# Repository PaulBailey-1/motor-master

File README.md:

# MotorMaster
This is a board designed to easily command FRC motors for testing or prototyping. It currently supports motors with the Talon FX motor controller. This repo contains the board schematics, PCB layout, and firmware for the board. 

## Features
It features 2 PWM channels that can be connected directly to the CAN connectors of the motor to command a duty cycle. Pressing the test button will output a 50% duty cycle on both PWM channels.  

The board can also be connected to motors through the CAN bus. Connect one end of the CAN chain to the CAN connector on the board and the other end to the TERM connector, or use another termination resistor. 
NOTE: CAN functionality is still experimental and may not work, feel free to work on it.

The e-stop button will prevent the board from outputting any commands until the MCU is reset with the reset button. 

The EXT pins can be used to connect an external input, like a switch or button, to provide additional control such as driving a motor or as an e-stop. The functionality must be added to the code, by default it does nothing.

The board can be powered through the USB C port, or from the power terminal off of a 12V battery. The board does not supply the motor with power, but it is important that it shares ground with the motor. 

The board is designed to be used over Bluetooth with its accompanying app, the source of which is here: https://github.com/PaulBailey-1/motor-master-app  
It is a cross-platform app and so should be able to be compiled for Android and iOS, but it has only been tested for Android. 

## Manufacturing
Board gerbers exported for manufacture by OSHPark are included in the repo, otherwise, the board can be opened in KiCad to export for manufacture. The BOM can be ordered from either Mouser or DigiKey.  

The FTDI header (J5) and the EXT header (J6) are optional. The USBC TVS diode (D2) may also be omitted since it is hard to solder without bridges, although it does make the USB lines vulnerable to damage from ESD. The USB C may also be omitted entirely (J1 & D2), and the board can be programmed through the FTDI header. 

To assemble the board, a stencil can be ordered and used to apply solder paste to the pads. The solder then may be reflowed in an oven or with hot air. It may also be possible to have it assembled by the PCB fab house.

## Programming
Dependencies:
* CAN by Sandeep Mistry v0.3.1
* ESP32Servo by Kevin Harrington & John K. Bennett v3.0.5

To program the board, connect to it with USB C or with an FTID adapter and program it with the Arduino IDE. Install the ESP32 boards and the required libraries, select 'ESP32S3 Dev Module' as the board, and upload.  

The name of the board over Bluetooth can have a postfix added to it in the code to help distinguish it.
The first time the board is programmed after being assembled, the Boot button must be held from when it is plugged until it has been flashed.
For debugging over USB C make sure the 'USB CDC On Boot' option is enabled so that you can get logging over the serial port.

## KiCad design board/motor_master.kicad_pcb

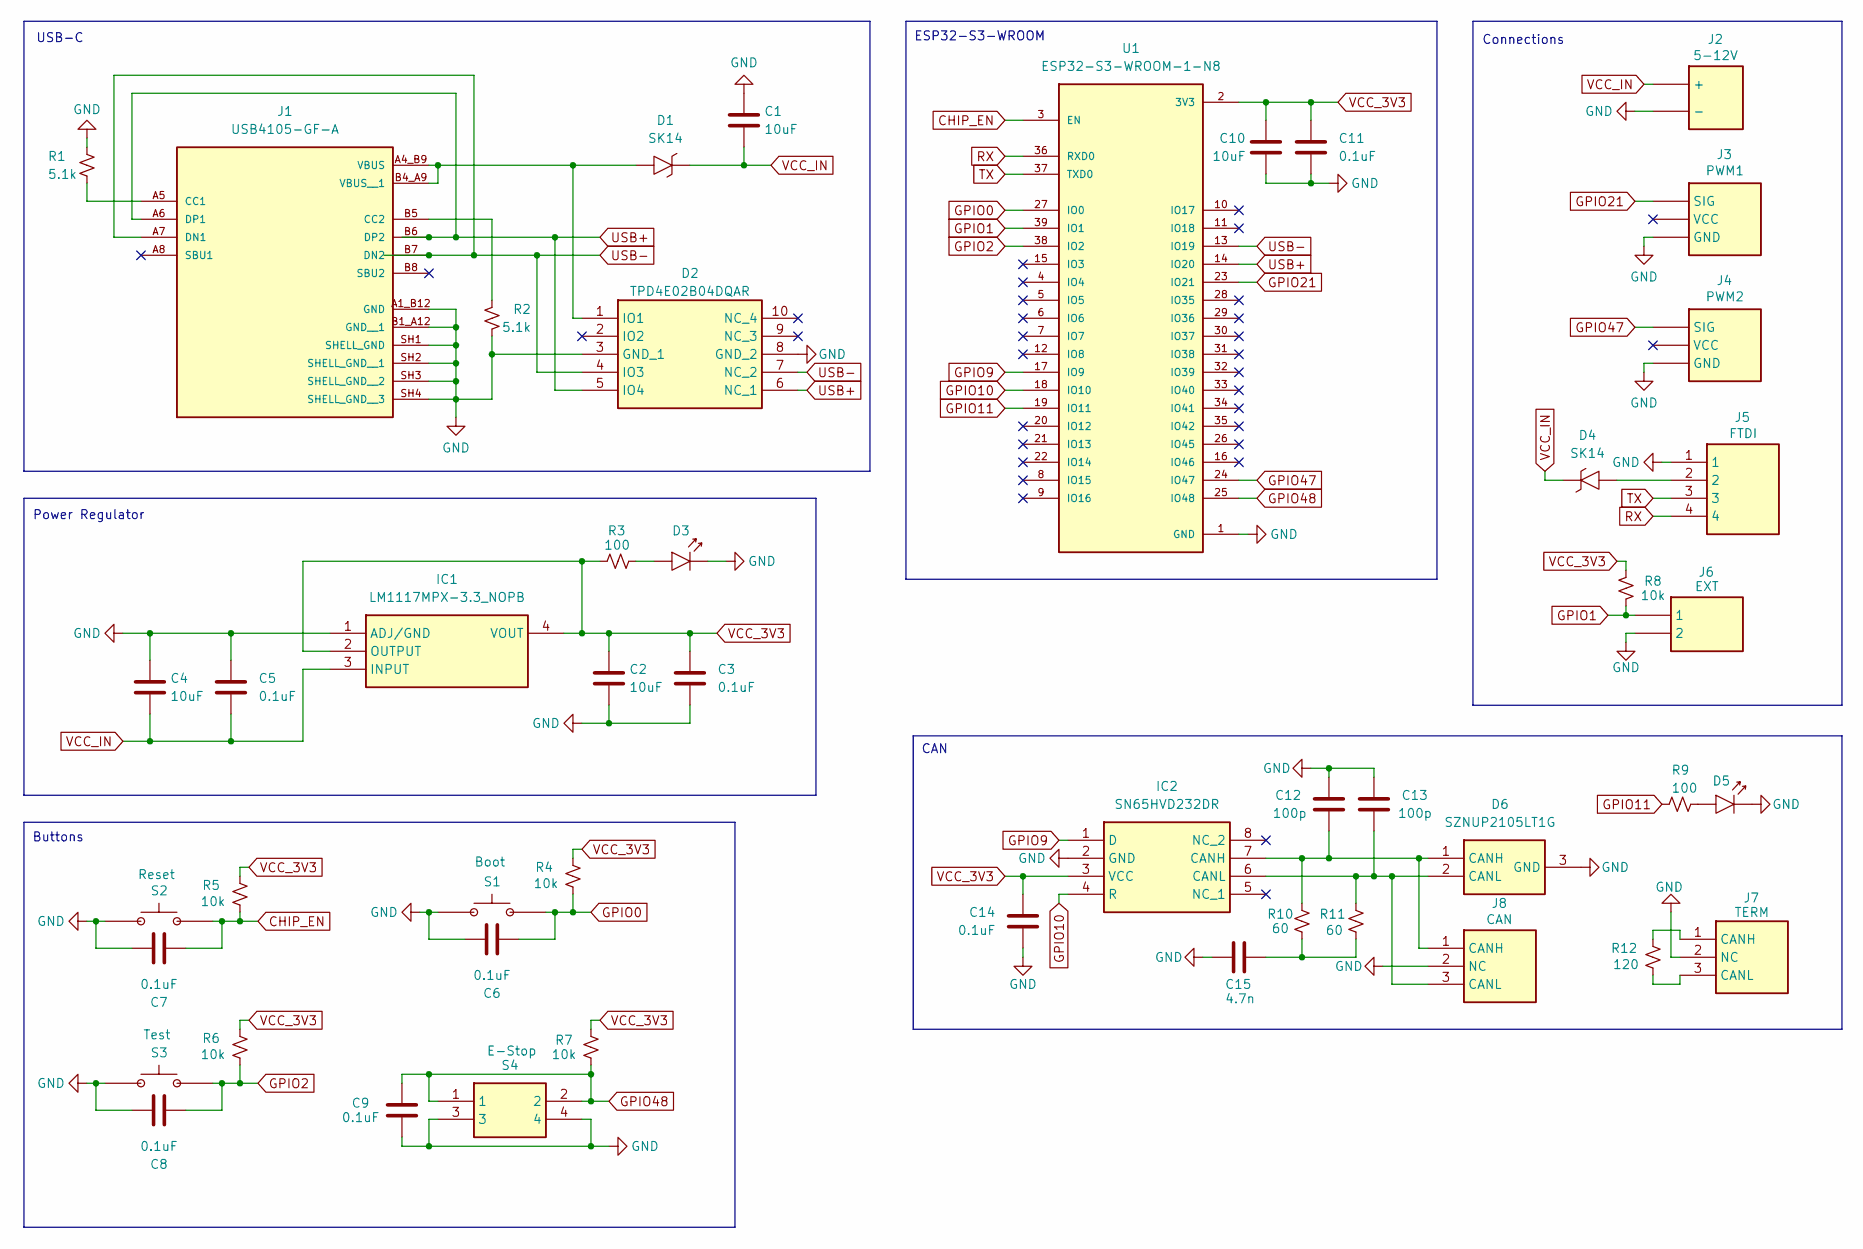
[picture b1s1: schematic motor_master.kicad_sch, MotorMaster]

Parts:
C1, C2, C4, C10: 10uF; C_0603_1608Metric
C3, C5, C6, C7, C8, C9, C11, C14: 0.1uF; C_0603_1608Metric
C12, C13: 100p; C_0603_1608Metric
C15: 4.7n; C_0603_1608Metric
D1, D4: SK14; DIONM5027X250N; Mouser Part Number 637-SK14
D2: TPD4E02B04DQAR; DQA_R-PUSON-N10_; Mouser Part Number 595-TPD4E02B04DQAR
D3, D5: 150060RS75000; LEDC1608X80N; Mouser Part Number 710-150060RS75000
D6: SZNUP2105LT1G; SOT96P237X111-3N; Mouser Part Number 863-SZNUP2105LT1G
IC1: LM1117MPX-3.3_NOPB; SOT230P700X180-4N; Mouser Part Number 926-LM1117MPX3.3NOPB
IC2: SN65HVD232DR; SOIC127P600X175-8N; Mouser Part Number 595-SN65HVD232DR
J1: USB4105-GF-A; GCT_USB4105-GF-A; PARTREV B3
J2: 5-12V; 1190297; Mouser Part Number 651-1190297
J3: PWM1; 1719710103; Mouser Part Number 200-TSW10307TS
J4: PWM2; 1719710103; Mouser Part Number 200-TSW10307TS
J5: FTDI; HDRV4W64P0X254_1X4_1016X254X889P; Mouser Part Number 855-M20-9990446
J6: EXT; TSW-102-XX-YY-S; Mouser Part Number 200-TSW10207TS
J7: TERM; 1719710103; Mouser Part Number 200-SSW10301FS
J8: CAN; 1719710103; Mouser Part Number 200-TSW10307TS
R1, R2: 5.1k; R_0603_1608Metric
R3, R9: 100; R_0603_1608Metric
R4, R5, R6, R7, R8: 10k; R_0603_1608Metric
R10, R11: 60; R_1206_3216Metric
R12: 120; R_0603_1608Metric
S1: Boot; PTS636SKG25JSMTRLFS; Mouser Part Number 611-PTS636SKG25JSMTR
S2: Reset; PTS636SKG25JSMTRLFS; Mouser Part Number 611-PTS636SKG25JSMTR
S3: Test; PTS636SKG25JSMTRLFS; Mouser Part Number 611-PTS636SKG25JSMTR
S4: E-Stop; FSM4JH; Mouser Part Number 506-FSM4JH
U1: ESP32-S3-WROOM-1-N8; XCVR_ESP32-S3-WROOM-1-N8

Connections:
CHIP_EN: C7.2, R5.1, S2.2 (NO), U1.3 (EN)
GND: C1.1, C2.2, C3.2, C4.1, C5.1, C6.1, C7.1, C8.1, C9.2, C10.2, C11.2, C12.2, C13.2, C14.1, C15.1, D2.3 (GND_1), D2.8 (GND_2), D3.2 (A), D5.2 (A), D6.3 (GND), IC1.1 (ADJ/GND), IC2.2 (GND), J1.A1_B12 (GND), J1.B1_A12 (GND__1), J1.SH1 (SHELL_GND), J1.SH2 (SHELL_GND__1), J1.SH3 (SHELL_GND__2), J1.SH4 (SHELL_GND__3), J2.3 (-), J2.4 (-), J3.3 (GND), J4.3 (GND), J5.1, J6.2, J7.2 (NC), J8.2 (NC), R1.1, R2.2, S1.1 (COM), S2.1 (COM), S3.1 (COM), S4.3, S4.4, U1.1 (GND), U1.40 (GND), U1.41_1 (GND), U1.41_2 (GND), U1.41_3 (GND), U1.41_4 (GND), U1.41_5 (GND), U1.41_6 (GND), U1.41_7 (GND), U1.41_8 (GND), U1.41_9 (GND)
GPIO0: C6.2, R4.1, S1.2 (NO), U1.27 (IO0)
GPIO1: J6.1, R8.1, U1.39 (IO1)
GPIO2: C8.2, R6.1, S3.2 (NO), U1.38 (IO2)
GPIO9: IC2.1 (D), U1.17 (IO9)
GPIO10: IC2.4 (R), U1.18 (IO10)
GPIO11: R9.2, U1.19 (IO11)
GPIO21: J3.1 (SIG), U1.23 (IO21)
GPIO47: J4.1 (SIG), U1.24 (IO47)
GPIO48: C9.1, R7.1, S4.1, S4.2, U1.25 (IO48)
unnamed: C15.2, R10.1, R11.1
unnamed: D1.2 (A), D2.1 (IO1), J1.A4_B9 (VBUS), J1.B4_A9 (VBUS__1)
unnamed: D3.1 (K), R3.1
unnamed: D4.2 (A), J5.2
unnamed: D5.1 (K), R9.1
unnamed: C12.1, D6.1 (CANH), IC2.7 (CANH), J8.1 (CANH), R10.2
unnamed: C13.1, D6.2 (CANL), IC2.6 (CANL), J8.3 (CANL), R11.2
unnamed: J1.A5 (CC1), R1.2
unnamed: J1.B5 (CC2), R2.1
unnamed: J7.1 (CANH), R12.2
unnamed: J7.3 (CANL), R12.1
RX: J5.4, U1.36 (RXD0)
TX: J5.3, U1.37 (TXD0)
USB+: D2.5 (IO4), D2.6 (NC_1), J1.A6 (DP1), J1.B6 (DP2), U1.14 (IO20)
USB-: D2.4 (IO3), D2.7 (NC_2), J1.A7 (DN1), J1.B7 (DN2), U1.13 (IO19)
VCC_3V3: C2.1, C3.1, C10.1, C11.1, C14.2, IC1.2 (OUTPUT), IC1.4 (VOUT), IC2.3 (VCC), R3.2, R4.2, R5.2, R6.2, R7.2, R8.2, U1.2 (3V3)
VCC_IN: C1.2, C4.2, C5.2, D1.1 (K), D4.1 (K), IC1.3 (INPUT), J2.1 (+), J2.2 (+)

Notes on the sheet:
USB-C
Connections
ESP32-S3-WROOM
CAN
Power Regulator
Buttons

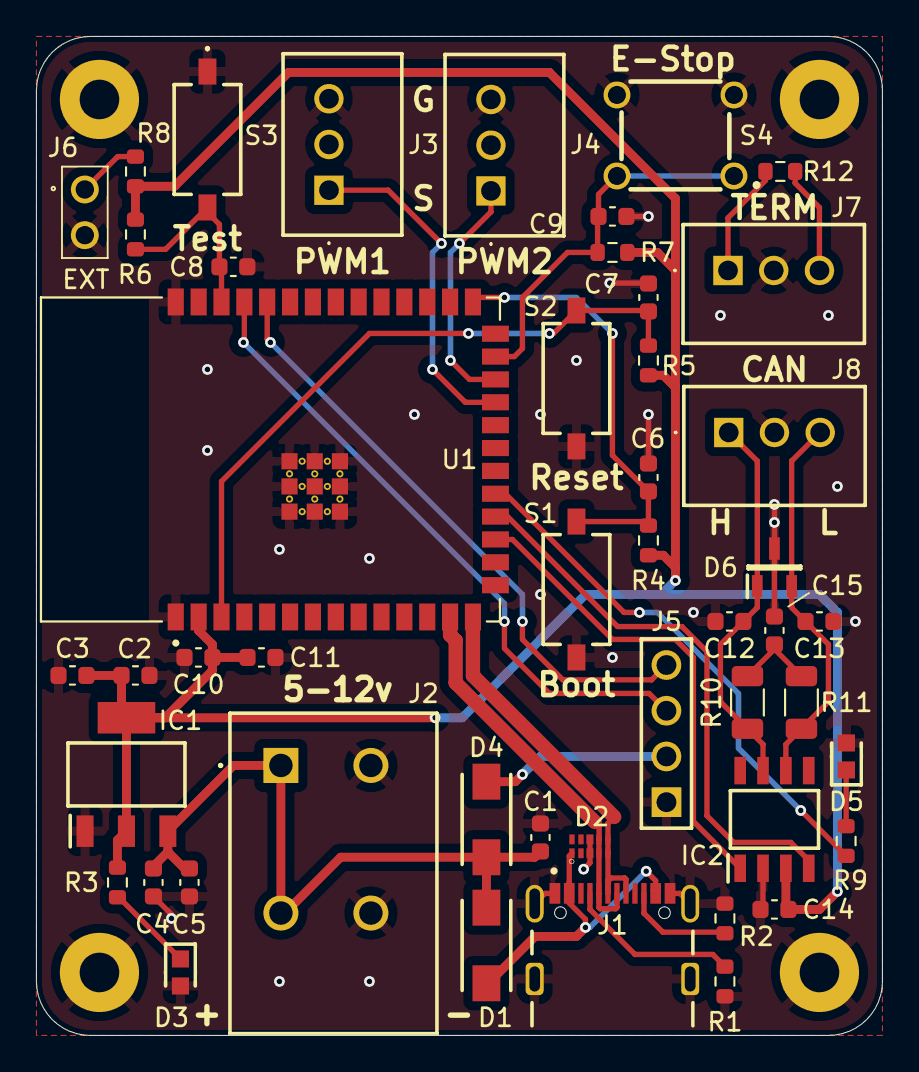
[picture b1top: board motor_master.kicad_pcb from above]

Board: 2 copper layers, 47.0 x 55.5 mm, 48 parts (0 on the bottom side), 28 nets.

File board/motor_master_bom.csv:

"Reference","Value","Qty","Mfr_Number","Supplier","Supplier_Number"
"C1,C2,C4,C10","10uF","4","C0603C106M9PAC","Mouser","80-C0603C106M9PAC"
"C3,C5,C6,C7,C8,C9,C11,C14","0.1uF","8","C0603C104K5RAC3121","Mouser","80-C603C104K5RAC3121"
"C12,C13","100p","2"," C0603C101J1GAC7411","Mouser","80-C0603C101J1GACLR"
"C15","4.7n","1"," C0603C472J5GACTU","Mouser","80-C0603C472J5G"
"D1,D4","SK14","2","SK14","Mouser","637-SK14"
"D2","TPD4E02B04DQAR","1","TPD4E02B04DQAR","Mouser","595-TPD4E02B04DQAR"
"D3","150060RS75000","1","150060RS75000","Mouser","710-150060RS75000"
"D5","150060RS75000","1","150060VS75000","Mouser","710-150060VS75000"
"D6","SZNUP2105LT1G","1","SZNUP2105LT1G","Mouser","863-SZNUP2105LT1G"
"IC1","LM1117MPX-3.3_NOPB","1","LM1117MPX-3.3/NOPB","Mouser","926-LM1117MPX3.3NOPB"
"IC2","SN65HVD232DR","1","SN65HVD232DR","Mouser","595-SN65HVD232DR"
"J1","USB4105-GF-A","1","USB4105-GF-A-120","Mouser","640-USB4105-GF-A-120"
"J2","5-12V","1","1190297","Mouser","651-1190297"
"J3,J4,J7,J8","-- mixed values --","4","705430002","Mouser","538-70543-0002"
"J5","FTDI","1","M20-9990446","Mouser","855-M20-9990446"
"J6","EXT","1","TSW-102-07-T-S","Mouser","200-TSW10207TS"
"R1,R2","5.1k","2","CRCW06035K10FKEA","Mouser","71-CRCW0603-5.1K-E3"
"R3,R9","100","2"," CRCW0603100RFKEA","Mouser","71-CRCW0603-100-E3"
"R4,R5,R6,R7,R8","10k","5","CRCW060310K0FKEA","Mouser","71-CRCW0603-10K-E3"
"R10,R11","60","2","CRCW120660R0KNAIF","Mouser","71-CRCW120660R0KNAIF"
"R12","120","1"," CRCW0603120RFKEA","Mouser","71-CRCW0603-120-E3"
"S1,S2,S3","-- mixed values --","3","PTS636 SKG25J SMTR LFS","Mouser","611-PTS636SKG25JSMTR"
"S4","E-Stop","1","FSM4JH","Mouser","506-FSM4JH"
"U1","ESP32-S3-WROOM-1-N8","1","ESP32-S3-WROOM-1-N8","Mouser","356-ESP32-S3WROOM1N8"

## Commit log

2024-07-15 init
2024-07-22 Board revisions from design review
2024-07-23 Changed power diodes
2024-07-26 Updated BOM with manufactuer numbers
2024-07-26 Added gerber
2024-08-19 Changed LEDs and fixed estop button wiring
2024-08-24 Added pullup resistor to extern pin, renumbered parts
2024-08-24 Added some framework for can, fixed some other bugs
2024-08-24 Update README.md with postFix comment
2024-08-24 Added optional postfix to BT name
